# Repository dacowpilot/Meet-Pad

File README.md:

# Meet-Pad
  
made in Shapr3D
# Features 

Meet-Pad is a hackpad that has 7 keys for shortcuts(like mute, camera, record, leave, etc.), a rotary encoder for volume control, and an OLED display screen for things like status. Like the name says, it will be used for shortcuts in meetings such as zoom calls and other meeting apps. The firmware might have a few bugs right now but I can fix it later once I get the XIAO.

# CAD

Made in Shapr3D.

# PCB

Made in KiCad.

# BOM

I already have a soldering iron so I don't need the soldering grant, but I do need the PCB and 3D printed case grant.  

Below are the parts I will be using to make my hackpad:  

• 1x XIAO RP2040  
• 7x Cherry MX Switches  
• 1x EC11 Rotary Encoder  
• 1x 0.91 inch OLED display  
• 7x White DSA Keycaps  
• 4x M3x16mm screws  
• 1x 3D printed case (1x Top Piece, 1x Bottom Piece, 1x Rotary Encoder Knob)
• 1x PCB board

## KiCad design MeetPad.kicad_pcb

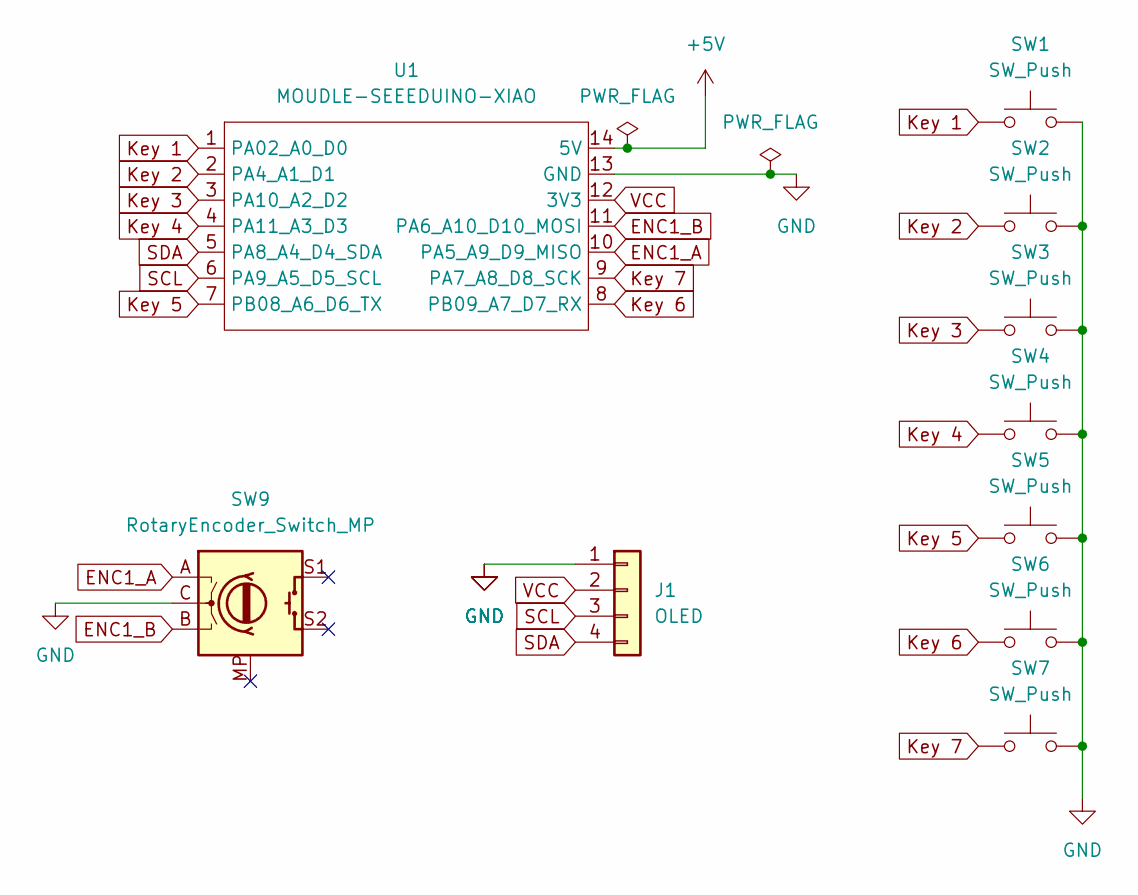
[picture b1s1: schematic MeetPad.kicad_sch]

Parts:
J1: OLED; FanPinHeader_1x04_P2.54mm_Vertical
SW1, SW2, SW3, SW4, SW5, SW6, SW7: SW_Push; SW_Cherry_MX_1.00u_PCB
SW9: RotaryEncoder_Switch_MP; RotaryEncoder_Alps_EC11E-Switch_Vertical_H20mm_MountingHoles
U1: MOUDLE-SEEEDUINO-XIAO; XIAO-Generic-Hybrid-14P-2.54-21X17.8MM

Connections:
+5V: U1.14 (5V)
ENC1_A: SW9.A, U1.10 (PA5_A9_D9_MISO)
ENC1_B: SW9.B, U1.11 (PA6_A10_D10_MOSI)
GND: J1.1, SW1.2, SW2.2, SW3.2, SW4.2, SW5.2, SW6.2, SW7.2, SW9.C, U1.13 (GND)
Key 1: SW1.1, U1.1 (PA02_A0_D0)
Key 2: SW2.1, U1.2 (PA4_A1_D1)
Key 3: SW3.1, U1.3 (PA10_A2_D2)
Key 4: SW4.1, U1.4 (PA11_A3_D3)
Key 5: SW5.1, U1.7 (PB08_A6_D6_TX)
Key 6: SW6.1, U1.8 (PB09_A7_D7_RX)
Key 7: SW7.1, U1.9 (PA7_A8_D8_SCK)
SCL: J1.3, U1.6 (PA9_A5_D5_SCL)
SDA: J1.4, U1.5 (PA8_A4_D4_SDA)
VCC: J1.2, U1.12 (3V3)

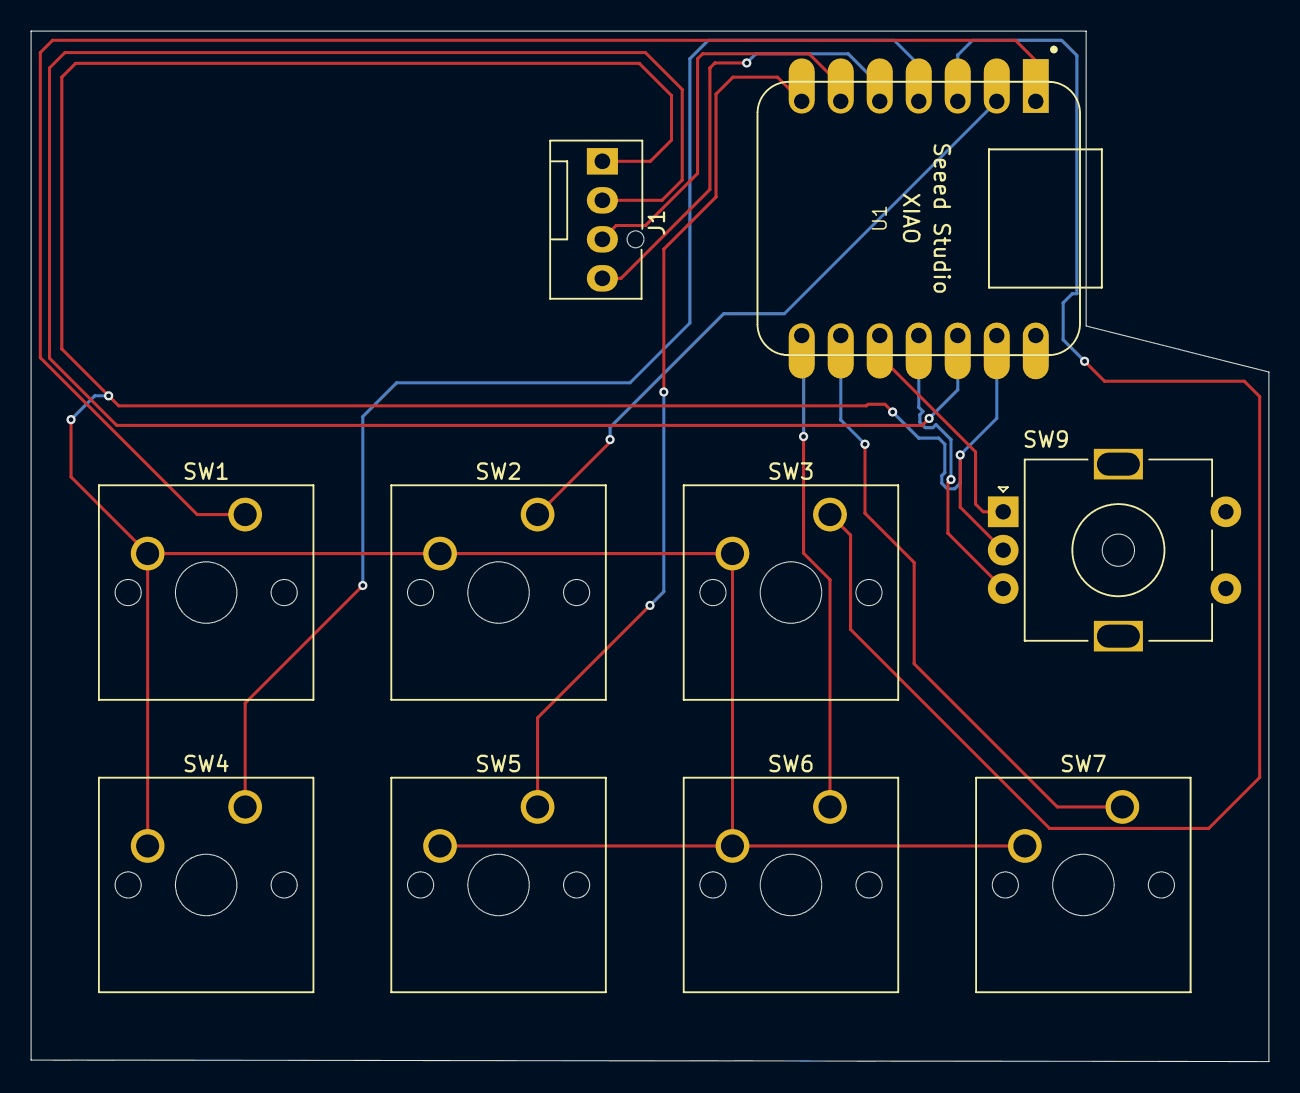
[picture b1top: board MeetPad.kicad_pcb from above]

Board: 2 copper layers, 80.6 x 67.1 mm, 10 parts (0 on the bottom side), 13 nets.
